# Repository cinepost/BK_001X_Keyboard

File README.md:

# BK_001X_Keyboard
Modern BK_0010/0011 Keyboard

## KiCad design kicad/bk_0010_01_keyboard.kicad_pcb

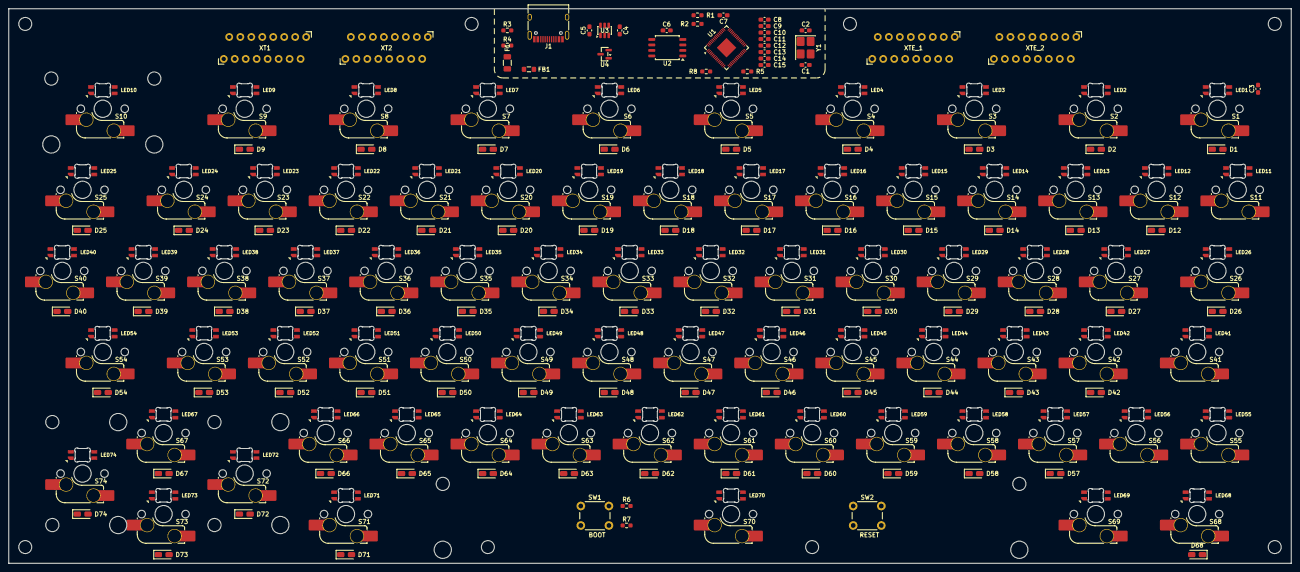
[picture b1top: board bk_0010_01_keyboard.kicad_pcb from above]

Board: 2 copper layers, 296.6 x 128.3 mm, 256 parts (0 on the bottom side), 188 nets, no tracks yet.

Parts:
C1, C2: 15p; C_0603_1608Metric_Pad1.08x0.95mm_HandSolder
C3: 100uF; C_0603_1608Metric_Pad1.08x0.95mm_HandSolder
C4, C5, C7: 1u; C_0603_1608Metric_Pad1.08x0.95mm_HandSolder
C6, C8, C9, C10, C11, C12, C13, C14, C15: 100nF; C_0603_1608Metric_Pad1.08x0.95mm_HandSolder
D1, D2, D3, D4, D5, D6, D7, D8, D9, D12, D13, D14, D15, D16, D17, D18, D19, D20, D21, D22, D23, D24, D25, D26, D27, D28, D29, D30, D31, D32, D33, D34, D35, D36, D37, D38, D39, D40, D42, D43, D44, D45, D46, D47, D48, D49, D50, D51, D52, D53, D54, D57, D58, D59, D60, D61, D62, D63, D64, D65, D66, D67, D68, D71, D72, D73, D74: 1N4148W; D_WITH_JP_SOD-123
F1: 1A; Fuse_1206_3216Metric
FB1: 100ohm 100MHz; L_0805_2012Metric_Pad1.05x1.20mm_HandSolder
J1: USB_C_Receptacle_USB2.0_16P; USB_C_Receptacle_HRO_TYPE-C-31-M-12
LED1, LED2, LED3, LED4, LED5, LED6, LED7, LED8, LED9, LED10, LED11, LED12, LED13, LED14, LED15, LED16, LED17, LED18, LED19, LED20, LED21, LED22, LED23, LED24, LED25, LED26, LED27, LED28, LED29, LED30, LED31, LED32, LED33, LED34, LED35, LED36, LED37, LED38, LED39, LED40, LED41, LED42, LED43, LED44, LED45, LED46, LED47, LED48, LED49, LED50, LED51, LED52, LED53, LED54, LED55, LED56, LED57, LED58, LED59, LED60, LED61, LED62, LED63, LED64, LED65, LED66, LED67, LED68, LED69, LED70, LED71, LED72, LED73, LED74: choc_SK6812MINI-E; LED_choc_6028R_18_75_reversed
R1, R2: 22R; R_0603_1608Metric_Pad0.98x0.95mm_HandSolder
R3, R4: 5.1K; R_0603_1608Metric_Pad0.98x0.95mm_HandSolder
R5, R6: 1K; R_0603_1608Metric_Pad0.98x0.95mm_HandSolder
R7: 10K/DNF; R_0603_1608Metric_Pad0.98x0.95mm_HandSolder
R8: 10K; R_0603_1608Metric_Pad0.98x0.95mm_HandSolder
S1: ПОВТ; SW_MX_18_75_1.5u
S2: КТ; SW_MX_18_75_1.5u
S3, S4, S5: SW_MX_18_75_1.5u
S6: ИНД СУ; SW_MX_18_75_1.5u
S7: БЛК РЕД; SW_MX_18_75_1.5u
S8: ШАГ; SW_MX_18_75_1.5u
S9: СБР; SW_MX_18_75_1.5u
S10: СТОП; SW_MX_18_75_2.0u
S11: SHIFT; SW_MX_18_75_1u
S12: ; +; SW_MX_18_75_1u
S13: 1 !; SW_MX_18_75_1u
S14: 2 "; SW_MX_18_75_1u
S15: 3 #; SW_MX_18_75_1u
S16: 4; SW_MX_18_75_1u
S17: 5 %; SW_MX_18_75_1u
S18: 6 &; SW_MX_18_75_1u
S19: 7; SW_MX_18_75_1u
S20: 8 (; SW_MX_18_75_1u
S21: 9 ); SW_MX_18_75_1u
S22: 0 {; SW_MX_18_75_1u
S23: - =; SW_MX_18_75_1u
S24: / <; SW_MX_18_75_1u
S25: ЗАБОЙ; SW_MX_18_75_1.5u
S26: ТАБ; SW_MX_18_75_1.5u
S27: Й J; SW_MX_18_75_1u
S28: Ц C; SW_MX_18_75_1u
S29: У U; SW_MX_18_75_1u
S30: К K; SW_MX_18_75_1u
S31: Е E; SW_MX_18_75_1u
S32: Н N; SW_MX_18_75_1u
S33, S53: Г G; SW_MX_18_75_1u
S34: Ш [; SW_MX_18_75_1u
S35: Щ ]; SW_MX_18_75_1u
S36: З Z; SW_MX_18_75_1u
S37: Х H; SW_MX_18_75_1u
S38: : *; SW_MX_18_75_1u
S39: Ъ }; SW_MX_18_75_1u
S40: ВС; SW_MX_18_75_1u
S41: СУ; SW_MX_18_75_1.5u
S42: Ф F; SW_MX_18_75_1u
S43: Ы Y; SW_MX_18_75_1u
S44: В W; SW_MX_18_75_1u
S45: A A; SW_MX_18_75_1u
S46: П P; SW_MX_18_75_1u
S47: Р R; SW_MX_18_75_1u
S48: О O; SW_MX_18_75_1u
S49: Л L; SW_MX_18_75_1u
S50: Д D; SW_MX_18_75_1u
S51: Ж V; SW_MX_18_75_1u
S52: Э \; SW_MX_18_75_1u
S54: ВВОД; SW_MX_18_75_1.5u
S55: ЗАГЛ; SW_MX_18_75_1u
S56: СТР; SW_MX_18_75_1u
S57: Я Q; SW_MX_18_75_1u
S58: Ч; SW_MX_18_75_1u
S59: С S; SW_MX_18_75_1u
S60: М M; SW_MX_18_75_1u
S61: И I; SW_MX_18_75_1u
S62: Т T; SW_MX_18_75_1u
S63: Ь X; SW_MX_18_75_1u
S64: Б B; SW_MX_18_75_1u
S65: Ю @; SW_MX_18_75_1u
S66: ;; SW_MX_18_75_1u
S67: UP; SW_MX_18_75_1u
S68: РУС; SW_MX_18_75_1.5u
S69: АР2; SW_MX_18_75_1u
S70: ПРОБЕЛ; SW_MX_18_75_1u
S71: ЛАТ; SW_MX_18_75_1.5u
S72: LEFT; SW_MX_18_75_2.0u_VERTICAL
S73: DOWN; SW_MX_18_75_1u
S74: RIGHT; SW_MX_18_75_2.0u_VERTICAL
STB1: STB_СТОП; STAB_MX_2u_18_75
STB2: STB_ВЛЕВО; STAB_MX_2u_18_75
STB3: STB_ВПРАВО; STAB_MX_2u_18_75
STB4: STB_ПРОБЕЛ; STAB_MX_8u_18_75
SW1: BOOT; SW_PUSH_6mm
SW2: RESET; SW_PUSH_6mm
U1: RP2040; QFN-56-1EP_7x7mm_P0.4mm_EP3.2x3.2mm
U2: W25Q16JVSS; SOIC-8_5.3x5.3mm_P1.27mm
U3: USBLC6-2SC6; SOT-23-6
U4: AP2127N-3.3; SOT-23
XT1, XT2: Conn_02x08_Top_Bottom; kbd_0001_01_xt_02x08
XTE_1, XTE_2: Conn_02x08_Top_Bottom; kbd_0001_01_xt_02x08
Y1: 12MHz; Crystal_SMD_3225-4Pin_3.2x2.5mm_HandSoldering

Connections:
+3.3V: C5.1, C6.1, C7.1, C8.2, C9.2, C10.2, C11.2, C12.2, C13.2, C14.2, R7.2, R8.2, U1.1 (IOVDD), U1.10 (IOVDD), U1.22 (IOVDD), U1.23 (DVDD), U1.33 (IOVDD), U1.42 (IOVDD), U1.44 (VREG_VIN), U1.45 (VREG_VOUT), U1.49 (IOVDD), U1.50 (DVDD), U2.8 (VCC), U4.2 (VO)
+5V: C3.1, C4.1, FB1.2, LED1.1 (VDD), LED2.1 (VDD), LED3.1 (VDD), LED4.1 (VDD), LED5.1 (VDD), LED6.1 (VDD), LED7.1 (VDD), LED8.1 (VDD), LED9.1 (VDD), LED10.1 (VDD), LED11.1 (VDD), LED12.1 (VDD), LED13.1 (VDD), LED14.1 (VDD), LED15.1 (VDD), LED16.1 (VDD), LED17.1 (VDD), LED18.1 (VDD), LED19.1 (VDD), LED20.1 (VDD), LED21.1 (VDD), LED22.1 (VDD), LED23.1 (VDD), LED24.1 (VDD), LED25.1 (VDD), LED26.1 (VDD), LED27.1 (VDD), LED28.1 (VDD), LED29.1 (VDD), LED30.1 (VDD), LED31.1 (VDD), LED32.1 (VDD), LED33.1 (VDD), LED34.1 (VDD), LED35.1 (VDD), LED36.1 (VDD), LED37.1 (VDD), LED38.1 (VDD), LED39.1 (VDD), LED40.1 (VDD), LED41.1 (VDD), LED42.1 (VDD), LED43.1 (VDD), LED44.1 (VDD), LED45.1 (VDD), LED46.1 (VDD), LED47.1 (VDD), LED48.1 (VDD), LED49.1 (VDD), LED50.1 (VDD), LED51.1 (VDD), LED52.1 (VDD), LED53.1 (VDD), LED54.1 (VDD), LED55.1 (VDD), LED56.1 (VDD), LED57.1 (VDD), LED58.1 (VDD), LED59.1 (VDD), LED60.1 (VDD), LED61.1 (VDD), LED62.1 (VDD), LED63.1 (VDD), LED64.1 (VDD), LED65.1 (VDD), LED66.1 (VDD), LED67.1 (VDD), LED68.1 (VDD), LED69.1 (VDD), LED70.1 (VDD), LED71.1 (VDD), LED72.1 (VDD), LED73.1 (VDD), LED74.1 (VDD), U3.5 (VBUS), U4.3 (VI)
/АР2: XT2.11, XTE_2.11
/ЗАГЛ: XT1.13, XTE_1.13
/ИНД: XT2.12, XTE_2.12
/ПРОБ: XT1.15, XTE_1.15
/СТР: XT1.14, XTE_1.14
/СУ: XT2.9, XTE_2.9
DN: R2.1, U3.4 (I/O2)
DP: R1.2, U3.3 (I/O2)
D_IN: LED1.3 (DIN), U1.29 (GPIO18)
D_OUT_1: LED10.2 (DOUT), LED11.3 (DIN)
D_OUT_2: LED20.2 (DOUT), LED21.3 (DIN)
D_OUT_3: LED30.2 (DOUT), LED31.3 (DIN)
D_OUT_4: LED40.2 (DOUT), LED41.3 (DIN)
D_OUT_5: LED50.2 (DOUT), LED51.3 (DIN)
D_OUT_6: LED60.2 (DOUT), LED61.3 (DIN), LED70.2 (DOUT)
D_USB_N: J1.A7 (D-), J1.B7 (D-), U3.6 (I/O1)
D_USB_P: J1.A6 (D+), J1.B6 (D+), U3.1 (I/O1)
GND: C1.2, C2.2, C3.2, C4.2, C5.2, C6.2, C7.2, C8.1, C9.1, C10.1, C11.1, C12.1, C13.1, C14.1, C15.1, J1.A1 (GND), J1.A12 (GND), J1.B1 (GND), J1.B12 (GND), J1.S1 (SHIELD), LED1.4 (VSS), LED2.4 (VSS), LED3.4 (VSS), LED4.4 (VSS), LED5.4 (VSS), LED6.4 (VSS), LED7.4 (VSS), LED8.4 (VSS), LED9.4 (VSS), LED10.4 (VSS), LED11.4 (VSS), LED12.4 (VSS), LED13.4 (VSS), LED14.4 (VSS), LED15.4 (VSS), LED16.4 (VSS), LED17.4 (VSS), LED18.4 (VSS), LED19.4 (VSS), LED20.4 (VSS), LED21.4 (VSS), LED22.4 (VSS), LED23.4 (VSS), LED24.4 (VSS), LED25.4 (VSS), LED26.4 (VSS), LED27.4 (VSS), LED28.4 (VSS), LED29.4 (VSS), LED30.4 (VSS), LED31.4 (VSS), LED32.4 (VSS), LED33.4 (VSS), LED34.4 (VSS), LED35.4 (VSS), LED36.4 (VSS), LED37.4 (VSS), LED38.4 (VSS), LED39.4 (VSS), LED40.4 (VSS), LED41.4 (VSS), LED42.4 (VSS), LED43.4 (VSS), LED44.4 (VSS), LED45.4 (VSS), LED46.4 (VSS), LED47.4 (VSS), LED48.4 (VSS), LED49.4 (VSS), LED50.4 (VSS), LED51.4 (VSS), LED52.4 (VSS), LED53.4 (VSS), LED54.4 (VSS), LED55.4 (VSS), LED56.4 (VSS), LED57.4 (VSS), LED58.4 (VSS), LED59.4 (VSS), LED60.4 (VSS), LED61.4 (VSS), LED62.4 (VSS), LED63.4 (VSS), LED64.4 (VSS), LED65.4 (VSS), LED66.4 (VSS), LED67.4 (VSS), LED68.4 (VSS), LED69.4 (VSS), LED70.4 (VSS), LED71.4 (VSS), LED72.4 (VSS), LED73.4 (VSS), LED74.4 (VSS), R3.1, R4.1, SW2.1 (A), SW2.2 (A), U1.19 (TESTEN), U1.57 (GND), U2.4 (GND), U3.2 (GND), U4.1 (GND), Y1.2 (G), Y1.4 (G)
unnamed: D1.2 (A), S1.2
unnamed: D2.2 (A), S2.2
unnamed: D3.2 (A), S3.2
unnamed: D4.2 (A), S4.2
unnamed: D5.2 (A), S5.2
unnamed: D6.2 (A), S6.2
unnamed: D7.2 (A), S7.2
unnamed: D8.2 (A), S8.2
unnamed: D9.2 (A), S9.2
unnamed: D12.2 (A), S12.2
unnamed: D13.2 (A), S13.2
unnamed: D14.2 (A), S14.2
unnamed: D15.2 (A), S15.2
unnamed: D16.2 (A), S16.2
unnamed: D17.2 (A), S17.2
unnamed: D18.2 (A), S18.2
unnamed: D19.2 (A), S19.2
unnamed: D20.2 (A), S20.2
unnamed: D21.2 (A), S21.2
unnamed: D22.2 (A), S22.2
unnamed: D23.2 (A), S23.2
unnamed: D24.2 (A), S24.2
unnamed: D25.2 (A), S25.2
unnamed: D26.2 (A), S26.2
unnamed: D27.2 (A), S27.2
unnamed: D28.2 (A), S28.2
unnamed: D29.2 (A), S29.2
unnamed: D30.2 (A), S30.2
unnamed: D31.2 (A), S31.2
unnamed: D32.2 (A), S32.2
unnamed: D33.2 (A), S33.2
unnamed: D34.2 (A), S34.2
unnamed: D35.2 (A), S35.2
unnamed: D36.2 (A), S36.2
unnamed: D37.2 (A), S37.2
unnamed: D38.2 (A), S38.2
unnamed: D39.2 (A), S39.2
unnamed: D40.2 (A), S40.2
unnamed: D42.2 (A), S42.2
unnamed: D43.2 (A), S43.2
unnamed: D44.2 (A), S44.2
unnamed: D45.2 (A), S45.2
unnamed: D46.2 (A), S46.2
unnamed: D47.2 (A), S47.2
unnamed: D48.2 (A), S48.2
unnamed: D49.2 (A), S49.2
unnamed: D50.2 (A), S50.2
unnamed: D51.2 (A), S51.2
unnamed: D52.2 (A), S52.2
unnamed: D53.2 (A), S53.2
unnamed: D54.2 (A), S54.2
unnamed: D57.2 (A), S57.2
unnamed: D58.2 (A), S58.2
unnamed: D59.2 (A), S59.2
unnamed: D60.2 (A), S60.2
unnamed: D61.2 (A), S61.2
unnamed: D62.2 (A), S62.2
unnamed: D63.2 (A), S63.2
unnamed: D64.2 (A), S64.2
unnamed: D65.2 (A), S65.2
unnamed: D66.2 (A), S66.2
unnamed: D67.2 (A), S67.2
unnamed: D68.2 (A), S68.2
unnamed: D71.2 (A), S71.2
unnamed: D72.2 (A), S72.2
unnamed: D73.2 (A), S73.2
unnamed: D74.2 (A), S74.2
unnamed: F1.1, J1.A4 (VBUS), J1.A9 (VBUS), J1.B4 (VBUS), J1.B9 (VBUS)
unnamed: F1.2, FB1.1
unnamed: J1.A5 (CC1), R3.2
unnamed: J1.B5 (CC2), R4.2
unnamed: LED1.2 (DOUT), LED2.3 (DIN)
unnamed: LED2.2 (DOUT), LED3.3 (DIN)
unnamed: LED3.2 (DOUT), LED4.3 (DIN)
unnamed: LED4.2 (DOUT), LED5.3 (DIN)
unnamed: LED5.2 (DOUT), LED6.3 (DIN)
unnamed: LED6.2 (DOUT), LED7.3 (DIN)
unnamed: LED7.2 (DOUT), LED8.3 (DIN)
unnamed: LED8.2 (DOUT), LED9.3 (DIN)
unnamed: LED9.2 (DOUT), LED10.3 (DIN)
unnamed: LED11.2 (DOUT), LED12.3 (DIN)
unnamed: LED12.2 (DOUT), LED13.3 (DIN)
unnamed: LED13.2 (DOUT), LED14.3 (DIN)
unnamed: LED14.2 (DOUT), LED15.3 (DIN)
unnamed: LED15.2 (DOUT), LED16.3 (DIN)
unnamed: LED16.2 (DOUT), LED17.3 (DIN)
unnamed: LED17.2 (DOUT), LED18.3 (DIN)
unnamed: LED18.2 (DOUT), LED19.3 (DIN)
unnamed: LED19.2 (DOUT), LED20.3 (DIN)
unnamed: LED21.2 (DOUT), LED22.3 (DIN)
unnamed: LED22.2 (DOUT), LED23.3 (DIN)
unnamed: LED23.2 (DOUT), LED24.3 (DIN)
unnamed: LED24.2 (DOUT), LED25.3 (DIN)
unnamed: LED25.2 (DOUT), LED26.3 (DIN)
unnamed: LED26.2 (DOUT), LED27.3 (DIN)
unnamed: LED27.2 (DOUT), LED28.3 (DIN)
unnamed: LED28.2 (DOUT), LED29.3 (DIN)
unnamed: LED29.2 (DOUT), LED30.3 (DIN)
unnamed: LED31.2 (DOUT), LED32.3 (DIN)
unnamed: LED32.2 (DOUT), LED33.3 (DIN)
unnamed: LED33.2 (DOUT), LED34.3 (DIN)
unnamed: LED34.2 (DOUT), LED35.3 (DIN)
unnamed: LED35.2 (DOUT), LED36.3 (DIN)
unnamed: LED36.2 (DOUT), LED37.3 (DIN)
unnamed: LED37.2 (DOUT), LED38.3 (DIN)
unnamed: LED38.2 (DOUT), LED39.3 (DIN)
unnamed: LED39.2 (DOUT), LED40.3 (DIN)
unnamed: LED41.2 (DOUT), LED42.3 (DIN)
unnamed: LED42.2 (DOUT), LED43.3 (DIN)
unnamed: LED43.2 (DOUT), LED44.3 (DIN)
unnamed: LED44.2 (DOUT), LED45.3 (DIN)
unnamed: LED45.2 (DOUT), LED46.3 (DIN)
unnamed: LED46.2 (DOUT), LED47.3 (DIN)
unnamed: LED47.2 (DOUT), LED48.3 (DIN)
unnamed: LED48.2 (DOUT), LED49.3 (DIN)
unnamed: LED49.2 (DOUT), LED50.3 (DIN)
unnamed: LED51.2 (DOUT), LED52.3 (DIN)
unnamed: LED52.2 (DOUT), LED53.3 (DIN)
unnamed: LED53.2 (DOUT), LED54.3 (DIN)
unnamed: LED54.2 (DOUT), LED55.3 (DIN)
unnamed: LED55.2 (DOUT), LED56.3 (DIN)
unnamed: LED56.2 (DOUT), LED57.3 (DIN)
unnamed: LED57.2 (DOUT), LED58.3 (DIN)
unnamed: LED58.2 (DOUT), LED59.3 (DIN)
unnamed: LED59.2 (DOUT), LED60.3 (DIN)
unnamed: LED61.2 (DOUT), LED62.3 (DIN)
unnamed: LED62.2 (DOUT), LED63.3 (DIN)
unnamed: LED63.2 (DOUT), LED64.3 (DIN)
unnamed: LED64.2 (DOUT), LED65.3 (DIN)
unnamed: LED65.2 (DOUT), LED66.3 (DIN)
unnamed: LED66.2 (DOUT), LED67.3 (DIN)
unnamed: LED67.2 (DOUT), LED68.3 (DIN)
unnamed: LED68.2 (DOUT), LED69.3 (DIN)
unnamed: LED69.2 (DOUT), LED70.3 (DIN)
unnamed: LED71.2 (DOUT), LED72.3 (DIN)
unnamed: LED72.2 (DOUT), LED73.3 (DIN)
unnamed: LED73.2 (DOUT), LED74.3 (DIN)
unnamed: R6.2, SW1.1 (A), SW1.2 (A)
unnamed: U1.52 (QSPI_SCLK), U2.6 (CLK)
unnamed: U1.53 (QSPI_SD0), U2.5 (DI/IO_{0})
unnamed: U1.55 (QSPI_SD1), U2.2 (DO/IO_{1})
unnamed: U1.54 (QSPI_SD2), U2.3 (~WP/IO_{2})
unnamed: U1.51 (QSPI_SD3), U2.7 (~HOLD/~RESET/IO_{3})
unnamed: C15.2, R8.1, U1.26 (RUN)
unnamed: R1.1, U1.46 (USB_DM)
unnamed: R2.2, U1.47 (USB_DP)
unnamed: R5.2, U1.21 (XOUT)
unnamed: R6.1, R7.1, U1.56 (~QSPI_SS), U2.1 (~CS)
X0: D1.1 (K), D2.1 (K), D6.1 (K), D7.1 (K), D8.1 (K), U1.2 (GPIO0), XT1.1, XTE_1.1
X1: D3.1 (K), D9.1 (K), D26.1 (K), D54.1 (K), D68.1 (K), D71.1 (K), D72.1 (K), U1.3 (GPIO1), XT1.2, XTE_1.2
X2: D4.1 (K), D5.1 (K), D40.1 (K), U1.4 (GPIO2), XT1.3, XTE_1.3
X3: D25.1 (K), D67.1 (K), D73.1 (K), D74.1 (K), U1.5 (GPIO3), XT1.4, XTE_1.4
X4: D13.1 (K), D14.1 (K), D15.1 (K), D16.1 (K), D17.1 (K), D18.1 (K), D19.1 (K), D22.1 (K), U1.6 (GPIO4), XT1.5, XTE_1.5
X5: D12.1 (K), D20.1 (K), D21.1 (K), D23.1 (K), D24.1 (K), D33.1 (K), D38.1 (K), D66.1 (K), U1.7 (GPIO5), XT1.6, XTE_1.6
X6: D28.1 (K), D31.1 (K), D42.1 (K), D45.1 (K), D50.1 (K), D53.1 (K), D64.1 (K), D65.1 (K), U1.8 (GPIO6), XT1.7, XTE_1.7
X7: D27.1 (K), D30.1 (K), D32.1 (K), D37.1 (K), D48.1 (K), D49.1 (K), D60.1 (K), D61.1 (K), U1.9 (GPIO7), XT1.9, XTE_1.9
X8: D29.1 (K), D44.1 (K), D46.1 (K), D47.1 (K), D51.1 (K), D57.1 (K), D59.1 (K), D62.1 (K), U1.11 (GPIO8), XT1.10, XTE_1.10
X9: D34.1 (K), D35.1 (K), D36.1 (K), D39.1 (K), D43.1 (K), D52.1 (K), D58.1 (K), D63.1 (K), U1.12 (GPIO9), XT1.11, XTE_1.11
X_IN: C2.1, U1.20 (XIN), Y1.1
X_OUT: C1.1, R5.1, Y1.3
Y0: S8.1, S20.1, S22.1, S25.1, S37.1, S46.1, S63.1, S65.1, S72.1, U1.13 (GPIO10), XT1.8, XT2.8, XTE_1.8, XTE_2.8
Y1: S1.1, S13.1, S21.1, S26.1, S43.1, S45.1, S57.1, S61.1, S74.1, U1.14 (GPIO11), XT2.1, XTE_2.1
Y2: S6.1, S14.1, S27.1, S36.1, S38.1, S47.1, S54.1, S64.1, S67.1, U1.15 (GPIO12), XT2.2, XTE_2.2
Y3: S2.1, S3.1, S12.1, S15.1, S28.1, S30.1, S34.1, S40.1, S59.1, S73.1, U1.16 (GPIO13), XT2.3, XTE_2.3
Y4: S7.1, S9.1, S16.1, S49.1, S50.1, S52.1, S62.1, S66.1, U1.17 (GPIO14), XT2.4, XTE_2.4
Y5: S17.1, S23.1, S29.1, S31.1, S35.1, S60.1, U1.18 (GPIO15), XT2.5, XTE_2.5
Y6: S4.1, S18.1, S32.1, S33.1, S42.1, S51.1, S58.1, S68.1, U1.27 (GPIO16), XT2.6, XTE_2.6
Y7: S5.1, S19.1, S24.1, S39.1, S44.1, S48.1, S53.1, S71.1, U1.28 (GPIO17), XT2.7, XTE_2.7
